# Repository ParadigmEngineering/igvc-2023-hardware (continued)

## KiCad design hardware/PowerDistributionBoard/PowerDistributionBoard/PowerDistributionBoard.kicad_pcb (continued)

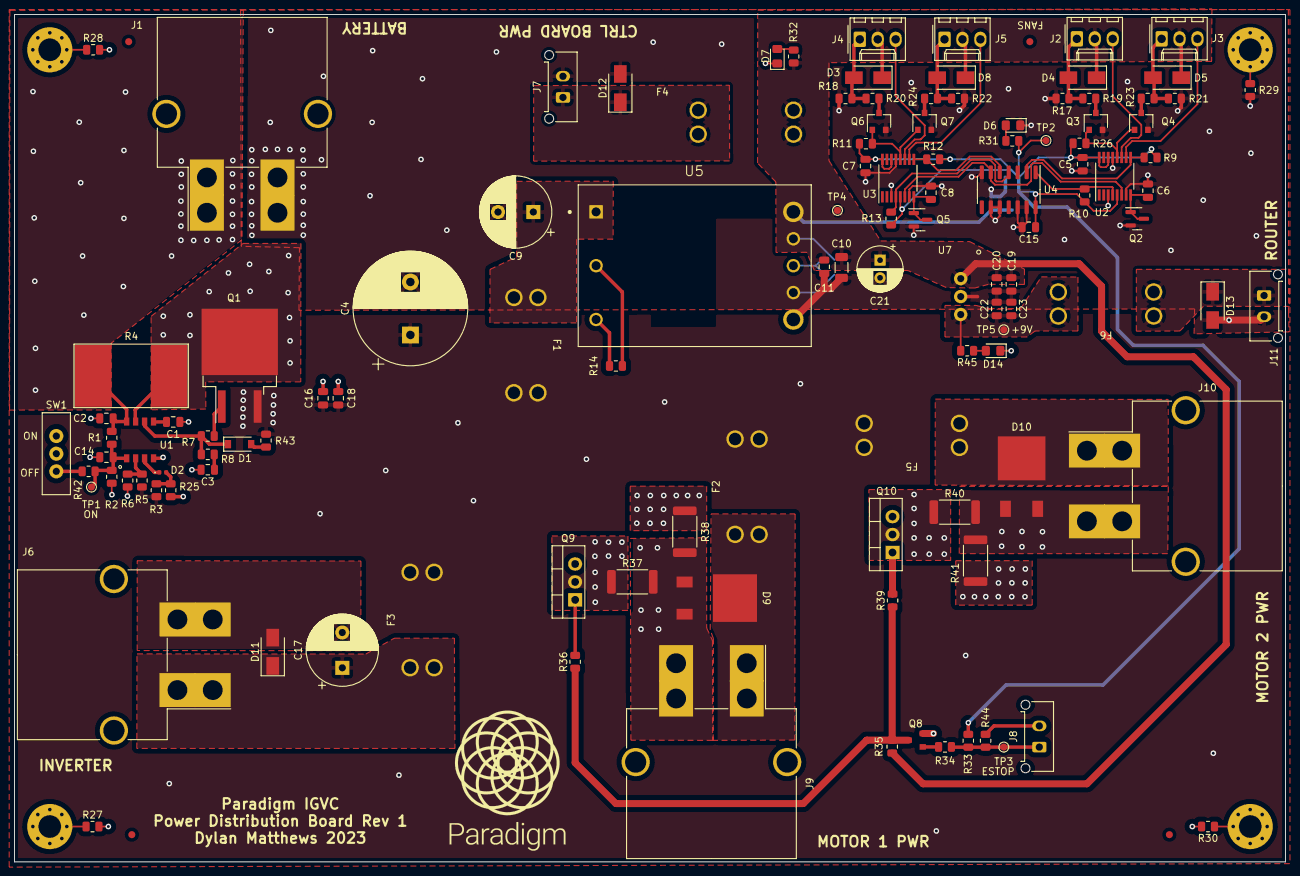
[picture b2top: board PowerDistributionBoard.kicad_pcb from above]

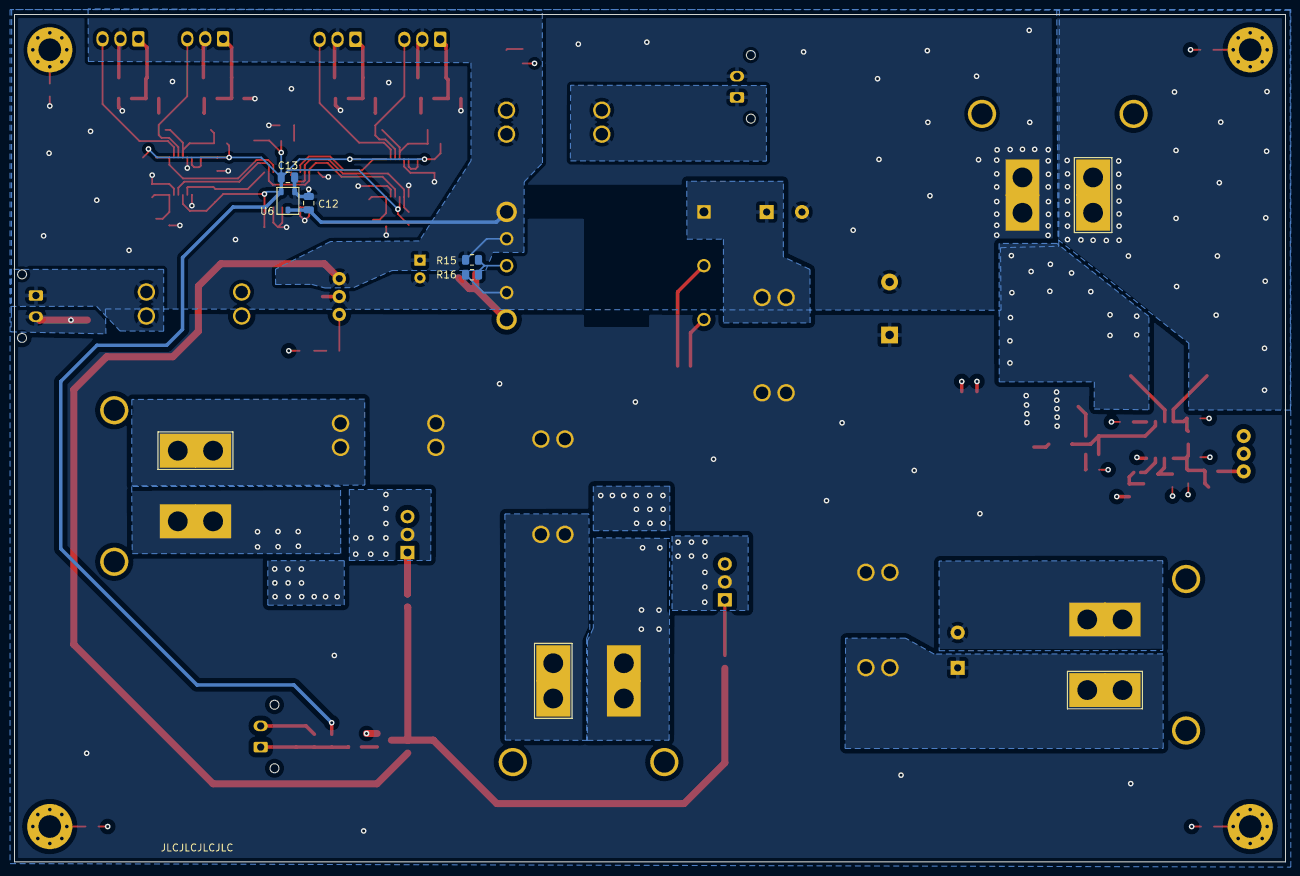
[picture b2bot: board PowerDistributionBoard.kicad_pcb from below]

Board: 4 copper layers, 180.0 x 120.0 mm, 130 parts (5 on the bottom side), 62 nets.

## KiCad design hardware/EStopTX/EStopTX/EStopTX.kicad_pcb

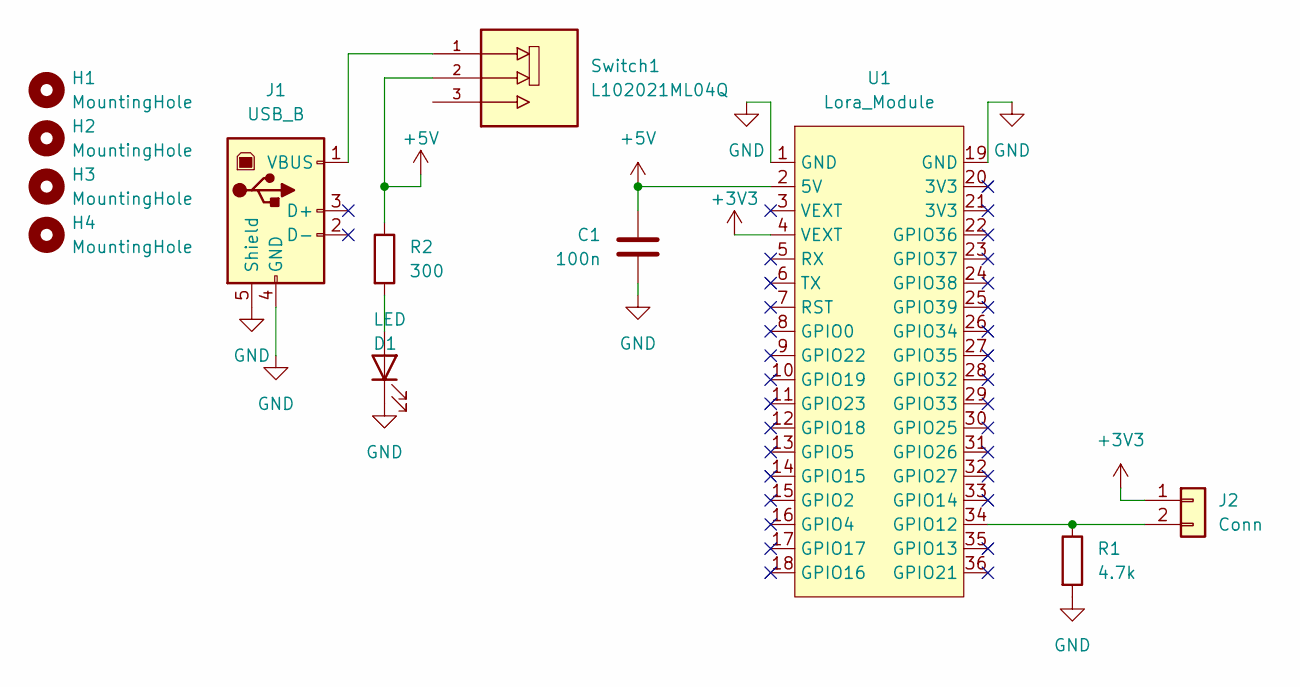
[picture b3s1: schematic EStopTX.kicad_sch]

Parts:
C1: 100n; C_Disc_D3.8mm_W2.6mm_P2.50mm; Digikey BC1084CT-ND
D1: LED; LED_D5.0mm
H1, H2, H3, H4: MountingHole; MountingHole_3.2mm_M3_Pad_Via
J1: USB_B; USB_B_OST_USB-B1HSxx_Horizontal
J2: Conn; Molex_Micro-Fit_3.0_43650-0200_1x02_P3.00mm_Horizontal
R1: 4.7k; R_Axial_DIN0207_L6.3mm_D2.5mm_P10.16mm_Horizontal
R2: 300; R_Axial_DIN0207_L6.3mm_D2.5mm_P10.16mm_Horizontal
Switch1: L102021ML04Q; SW_L102021ML04Q; Digikey CKC5102-ND
U1: Lora_Module

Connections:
+3V3: J2.1, U1.4 (VEXT)
+5V: C1.2, R2.1, Switch1.2, U1.2 (5V)
GND: C1.1, D1.1 (K), J1.4 (GND), J1.5 (Shield), R1.2, U1.1 (GND), U1.19 (GND)
unnamed: D1.2 (A), R2.2
unnamed: J1.1 (VBUS), Switch1.1
unnamed: J2.2, R1.1, U1.34 (GPIO12)

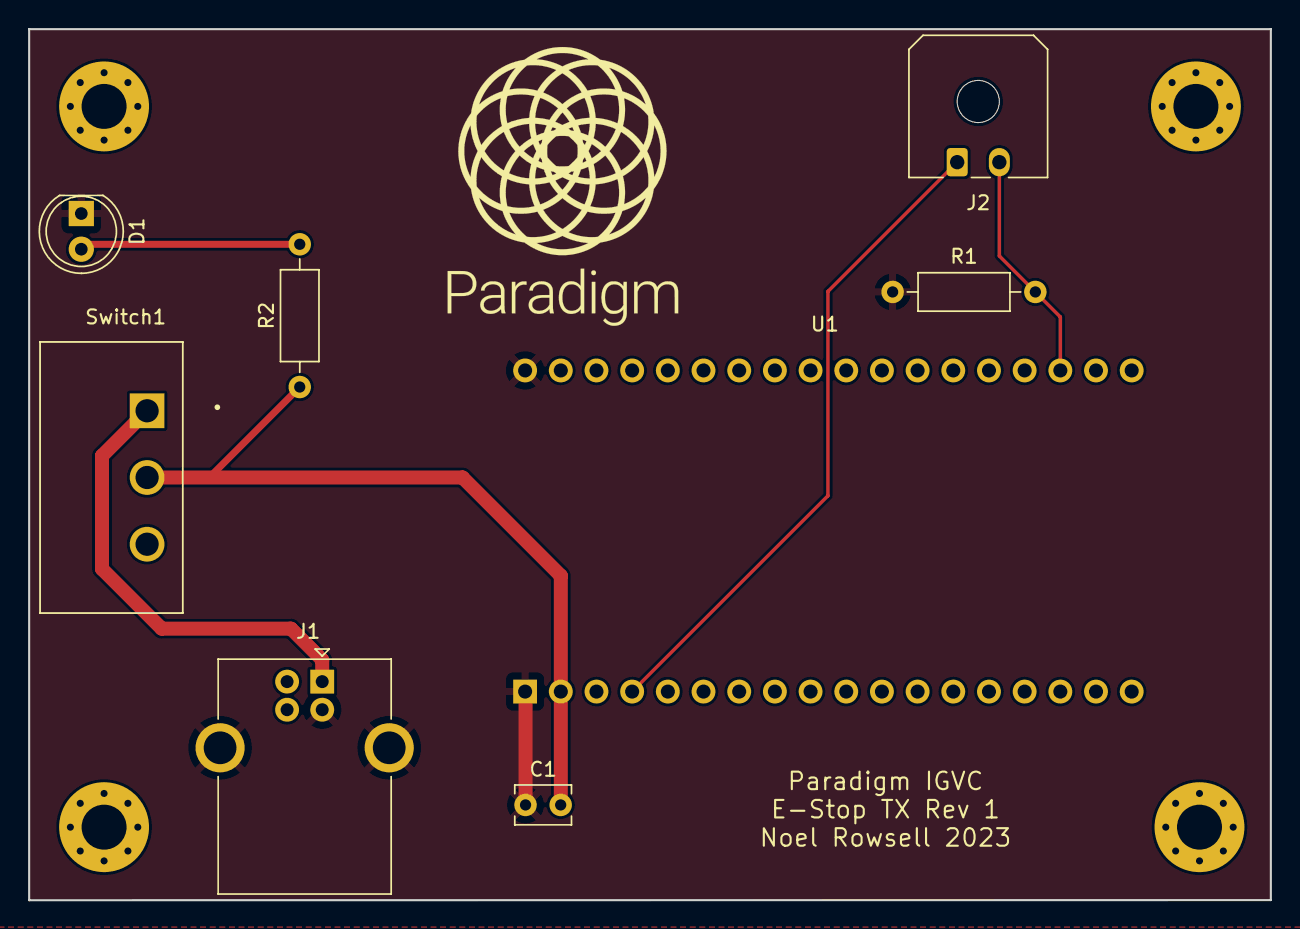
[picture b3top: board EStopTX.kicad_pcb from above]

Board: 2 copper layers, 88.4 x 62.0 mm, 12 parts (0 on the bottom side), 6 nets.

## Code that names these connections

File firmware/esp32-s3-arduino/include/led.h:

/**  @file led.h
 *   @brief LED Drivers that flash periodically based on the state of the bot.
 *          
 *   flash_leds() flashes the LEDs on a set frequency based on the state of the bot.
*/

#define LAMP1_ON 4
#define LAMP2_ON 5
#define LAMP3_ON 2
#define LAMP4_ON 1

#define DEBUG_LED 10

extern long int previous_time;
extern bool     previous_toggle;

/*
 * @brief If the bot is in STANDBY, have the LEDs be on solid. Otherwise if the
 *        bot is in the AUTONOMOUS control state, toggle LEDs every 0.25s,
 *        otherwise if the bot is in the MANUAL control state, toggle LEDs every 2s
 */
void flash_leds(void);

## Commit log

2023-01-02 PDB initial commit
2023-01-04 Fan Control
2023-01-26 Add 12V DC-DC and Estop Relays
2023-01-26 Added Resistor Options on Fans
2023-01-27 Add 3v3 LDO and Some Test Points
2023-01-29 Small stuff
2023-02-03 Add footprints and start layout on PDB, start control board schematic
2023-02-05 Layout Attempt 1
2023-02-15 PDB Routing First Pass
2023-02-15 Added step
2023-02-21 Estop Stuff
2023-02-22 More Estop Work
2023-02-23 PDB Review
    Added a few grounding vias to pads.
2023-02-24 Updating libraries
    Updated libraries. need to finish making changes to schematic.
2023-02-25 begin adding ESP32 stuff
2023-02-25 Fix Battery Connector, FET Footprint
2023-02-25 Small Changes
2023-02-26 Revert "Pushing current status of control board"
    This reverts commit 294db83ea49ed79939e01bc2aaba512b205aee08, reversing
    changes made to 02a1c7b732454ead7e64c67e54126222b2bb5f3d.
2023-02-26 Revert "Revert "Pushing current status of control board""
    This reverts commit 0a3f5a1237bc2ff3169470f75d528978fa5c2770.
2023-02-26 Revert "Revert "Revert "Pushing current status of control board"""
    This reverts commit d2dbbc2e3509cd4690ee25a171fb3cea29603b1d.
2023-03-01 More work on control board
2023-03-03 stuff
2023-03-08 ESP Fixes, Add Motor Controller Interface
2023-03-09 Add bypass for relay control BJT
2023-03-13 Motor Control with ESP/Estop
2023-03-15 Finish (?) micro stuff, define components, add UART header
2023-03-17 Control Board Power Changes
2023-03-17 Add note
2023-03-18 Fix Regulators, Change LORA Module Supply
2023-03-18 Starting Control Board Layout
2023-03-19 More Layout
2023-03-20 Start Control Board Routing
2023-03-21 Motor Controller IO Fixes
2023-03-22 Motor control stuff
2023-03-23 Control Board Routing Work
2023-03-24 Routing Work
2023-03-25 More Control Board Routing Stuff
2023-03-26 JLCPCB Part #'s added and footprints verified
    Checked footprints of LDOs and ICs on the board with data sheets
2023-03-27 Fix ESP Part Number
2023-03-28 Fix Pull-ups on Level Shifters
2023-03-31 Start Review Fixes
2023-04-01 Schematic Fixes: IO Translators, Safety Light FETs
2023-04-04 Fixing the things
2023-04-04 EStop TX Initial Commit
2023-04-05 Control Board - Replace LDOs, Fix ESP Strapping Pins, W EStop Voltage Divider
2023-04-06 Most control board schematic fixes done
2023-04-08 Control Board Rerouting
2023-04-08 continue board
2023-04-09 Things
2023-04-09 maybe done?
2023-04-09 Finish Control Board Routing
2023-04-09 Control Board Routing Tweaks
2023-04-10 PDB schematic - Add router power, address review comments
2023-04-11 adjustments
2023-04-12 Replace Relays with FETs for Motor Power Switching
2023-04-13 Power Board Changes
2023-04-14 PDB Hot Swap Circuit Changes/Review, Add Flybacks
2023-04-15 Power Board Schematic Revision Done, Fix Lora Symbol and Update Control Board Routing
2023-04-16 PDB Layout
2023-04-16 PDB routing V2 first pass
2023-04-19 Switch 5V LDO for DC DC
2023-04-20 hopefully done
2023-04-20 Estop review
2023-04-21 Last things
2023-04-21 PDB Assembly PNs
2023-04-23 Finish adding assembly PNs
2023-04-24 Build Files
2023-04-26 Control Board Silk Update
2023-05-01 Estop Firmware
2023-05-10 Hello World project for esp32-s3 arduino framework
2023-05-17 Driver implementations work in progress
2023-05-17 Polished fw, validation needed
2023-05-19 Polish PWM forward and reverse control, validation TBD
2023-05-28 Current validation work in progress
2023-06-05 Motor controller alarm fix (?)
